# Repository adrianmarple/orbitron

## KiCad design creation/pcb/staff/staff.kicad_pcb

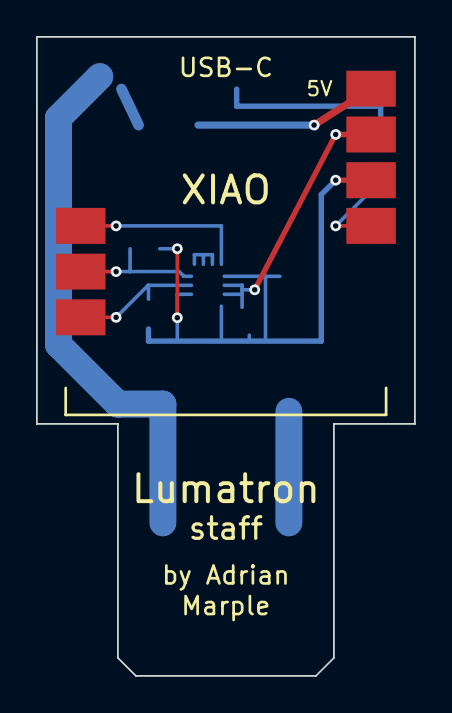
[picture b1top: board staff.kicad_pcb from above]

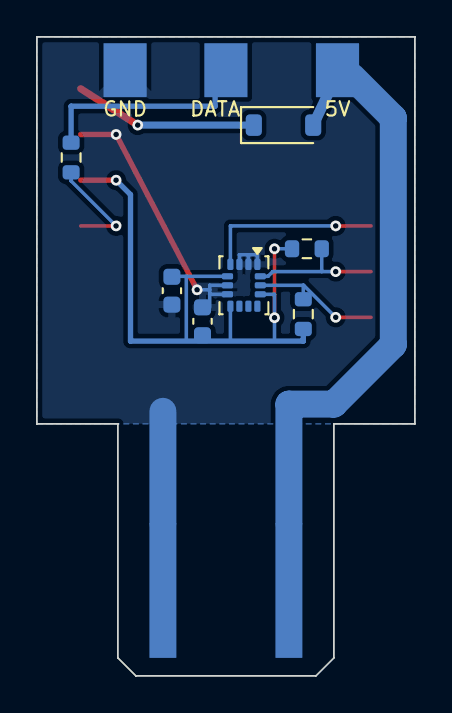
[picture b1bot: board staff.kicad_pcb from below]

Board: 2 copper layers, 21.0 x 35.5 mm, 12 parts (11 on the bottom side), 9 nets.

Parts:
C1, C2: 100nF; C_0603_1608Metric
D1: B5819W; D_SOD-123
J1: GND
J2: DATA
J3: 5V
J4: USB-A plug (PCB edge)
R1, R2: 4.7k; R_0603_1608Metric
R3: 330; R_0603_1608Metric
U1: LSM6DSV16X; LGA-14_3x2.5mm_P0.5mm_LayoutBorder3x4y
U2: XIAO ESP32 (SMD)

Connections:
3V3: C1.1, C2.2, R1.1, R2.1, U1.5, U1.8, U1.12, U2.12
5V: D1.2, J3.1, J4.1
5V_XIAO: D1.1, U2.14
D10: R3.1, U2.11
DATA: J2.1, R3.2
GND: C1.2, C2.1, J1.1, J4.4, U1.1, U1.2, U1.3, U1.6, U1.7, U2.13
INT1: U1.4, U2.4
SCL: R2.2, U1.13, U2.6
SDA: R1.2, U1.14, U2.5

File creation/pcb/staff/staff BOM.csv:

Comment,Designator,Footprint,LCSC
LSM6DSV16XTR,U1,LGA-14L 2.5x3mm,C5267406
100nF,"C1,C2",0603,C14663
4.7k,"R1,R2",0603,C23162
330,R3,0603,C23138
B5819W,D1,SOD-123,C8598
